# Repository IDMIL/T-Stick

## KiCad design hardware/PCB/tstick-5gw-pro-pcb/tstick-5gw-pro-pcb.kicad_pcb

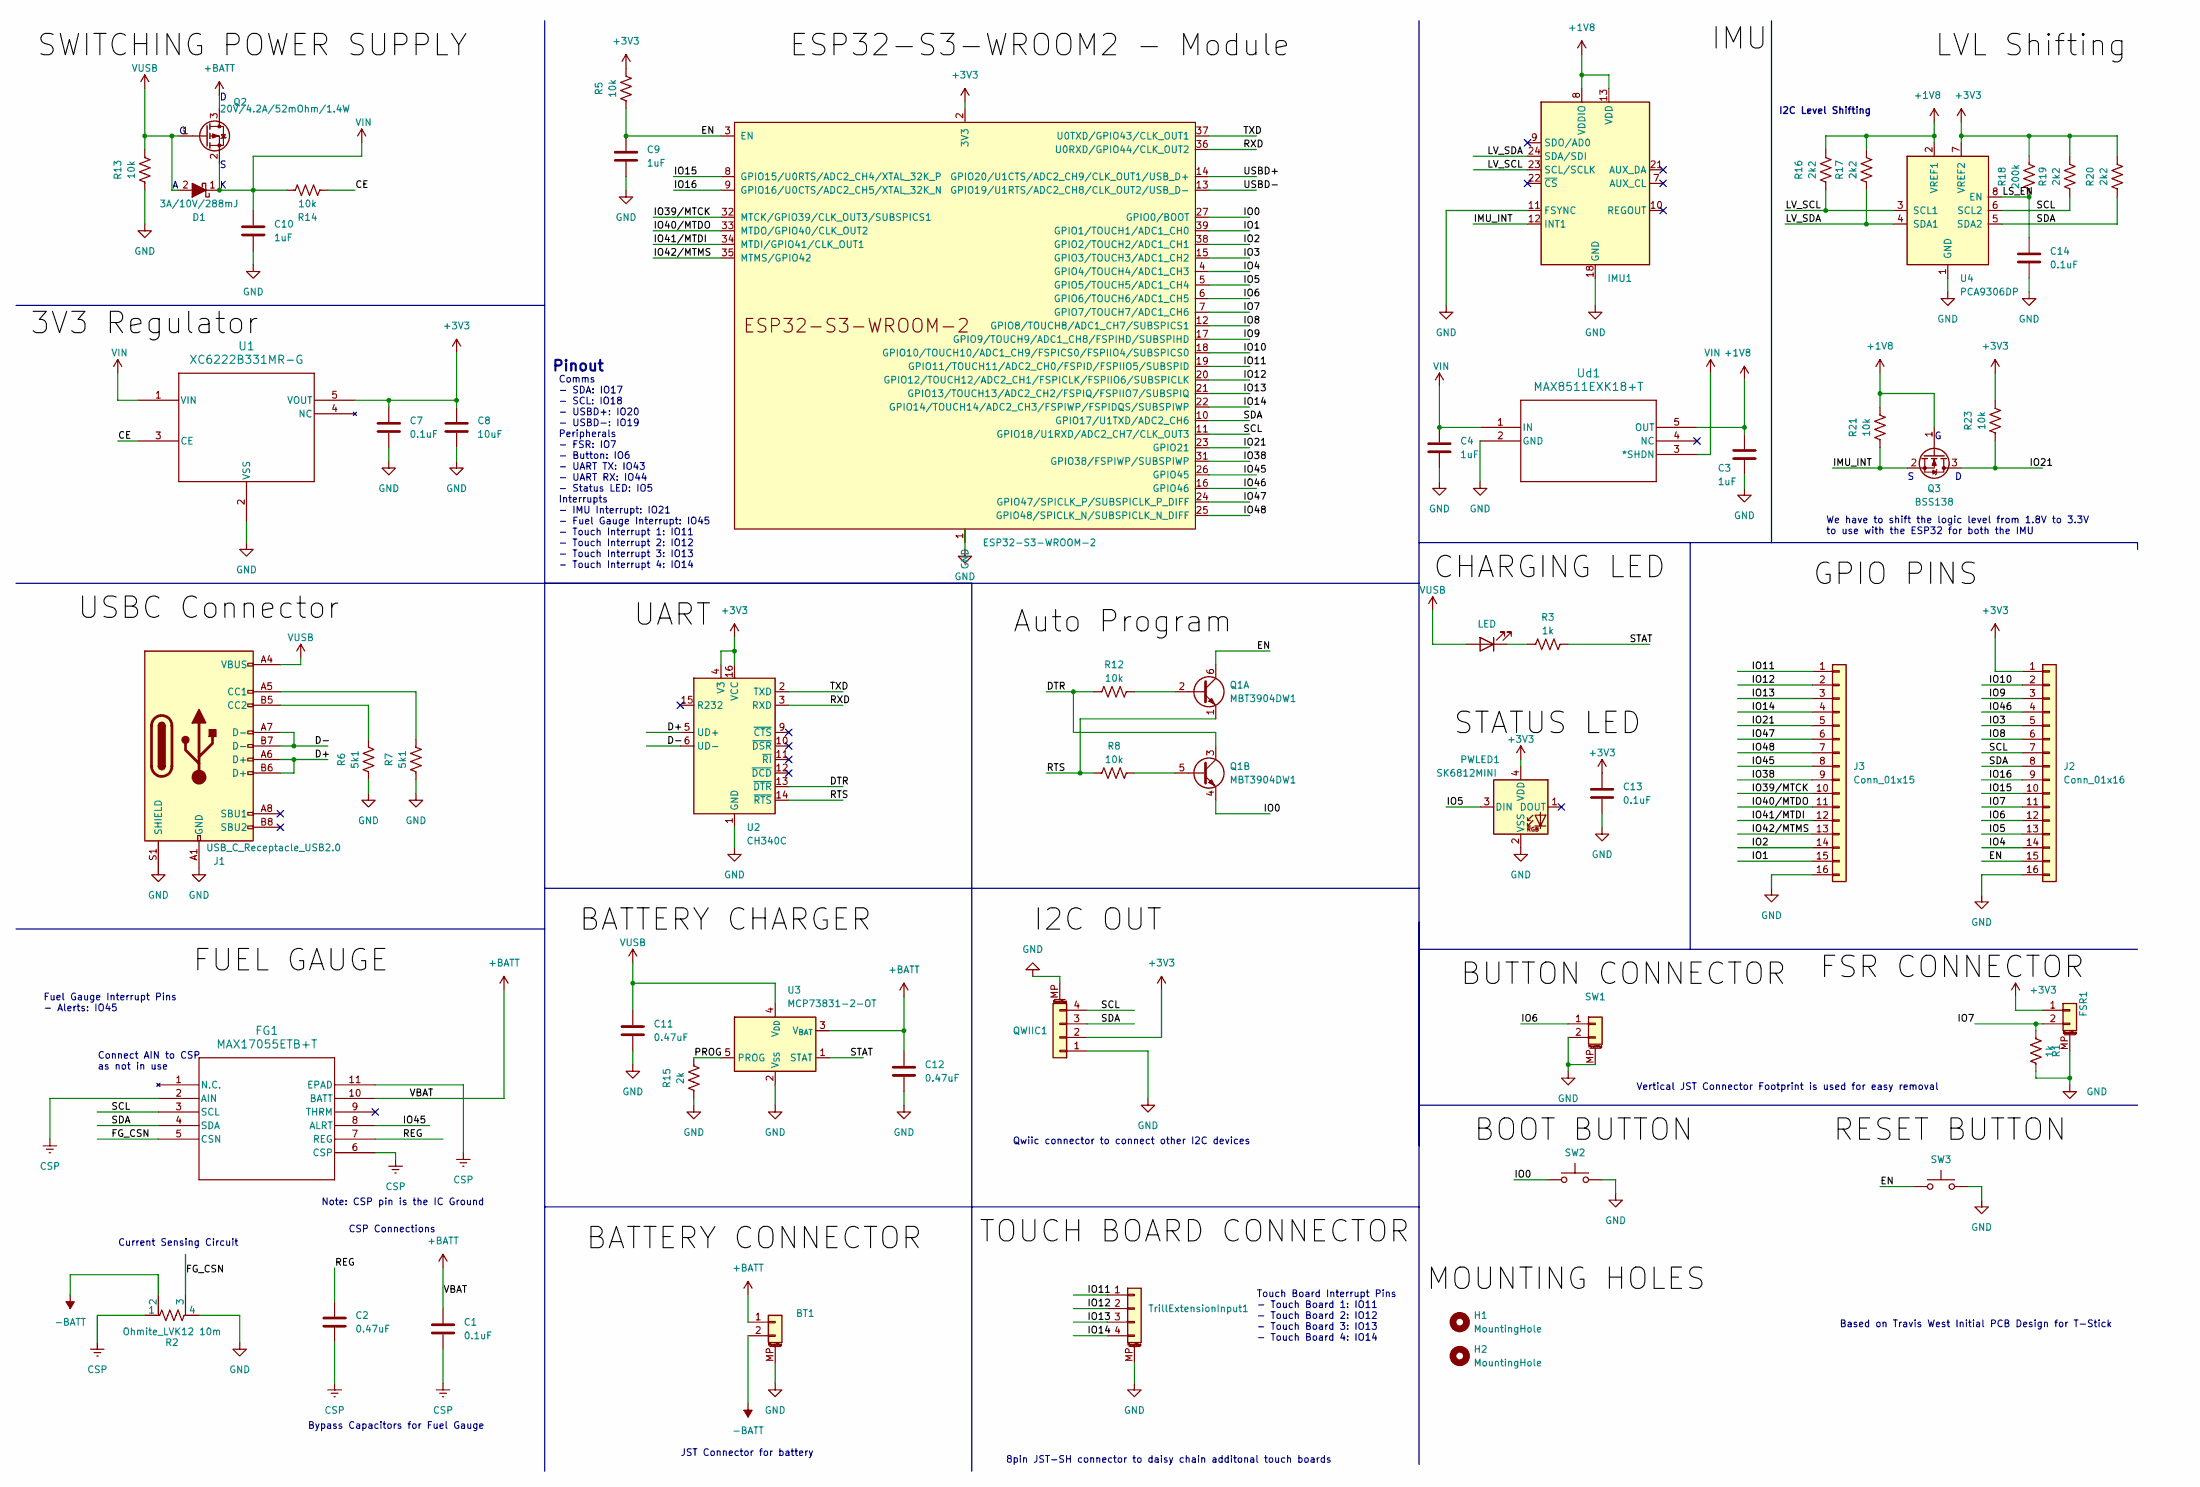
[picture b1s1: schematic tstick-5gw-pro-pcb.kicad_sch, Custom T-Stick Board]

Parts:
BT1: JST-PH-1x02-2.000mm; JST_PH_S2B-PH-SM4-TB_1x02-1MP_P2.00mm_Horizontal; Mfg Part # S2B-PH-SM4-TB; Digikey Part # 455-S2B-PH-SM4-TBTR-ND
C1: 0.1uF; C_0201_0603Metric; Mfg Part # CL03A104KP3NNNC; Digikey Part # 1276-1115-2-ND
C2, C11, C12: 0.47uF; C_0201_0603Metric; Mfg Part # CL03A474KQ3NNNC; Digikey Part # 1276-1337-1-ND
C3, C4: 1uF; C_0201_0603Metric; Mfg Part # CL03A105KQ3CSNC; Digikey Part # 1276-1115-1-ND
C7, C13, C14: 0.1uF; C_0201_0603Metric; Mfg Part # CL03A104KP3NNNC; Digikey Part # 1276-1115-1-ND
C8: 10uF; C_0603_1608Metric; Mfg Part # CL10A106KQ8NNNC; Digikey Part # 1276-1038-1-ND
C9, C10: 1uF; C_0201_0603Metric; Mfg Part # CL03A105KQ3CSNC; Digikey Part # 1276-1323-1-ND
CHARGLED1: LED; LED_0201_0603Metric; Mfg Part # APG0603ZGC-5MAV; Digikey Part # 754-APG0603ZGC-5MAVCT-ND
D1: 3A/10V/288mJ; D_SOD-323; Mfg Part # BAT60BE6327HTSA1; Digikey Part # BAT60BE6327HTSA1CT-ND
FG1: MAX17055ETB+T; 21-100013A_T102A2&plus_1C_MXM; Mfg Part # MAX17055ETB+T; Digikey Part # MAX17055ETB+TCT-ND
FSR1: JST-SH-1.00mm 1x2; JST_SH_BM02B-SRSS-TB_1x02-1MP_P1.00mm_Vertical; Mfg Part # BM02B-SRSS-TB; Digikey Part # 455-1788-1-ND
H1, H2: MountingHole; MountingHole_3.2mm_M3_DIN965
IMU1: ICM-20948; QFN24_3X3X0P9_IVS; Mfg Part # ICM-20948; Digikey Part # 1428-1123-1-ND
J1: USB_C_Receptacle_USB2.0; USB_C_Receptacle_GCT_USB4105-xx-A_16P_TopMnt_Horizontal; Mfg Part # USB4105-GF-A; Digikey Part # 2073-USB4105-GF-ACT-ND
J2: Conn_01x16; PinHeader_1x16_P2.54mm_Vertical
J3: Conn_01x15; PinHeader_1x16_P2.54mm_Vertical
MCU1: ESP32-S3-WROOM-2; Mfg Part # ESP32-S3-WROOM-2-N32R8V; Digikey Part # 1965-ESP32-S3-WROOM-2-N32R8VCT-ND
PWLED1: SK6812MINI; LED_SK6812MINI_PLCC4_3.5x3.5mm_P1.75mm; Mfg Part # Addressable Lighting Neopixel 10 LED Di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; Digikey Part # 1528-1542-ND
Q1: MBT3904DW1; SOT-363_SC-70-6; Mfg Part # MBT3904DW1T1G
Q2: 20V/4.2A/52mOhm/1.4W; SOT-23-3; Mfg Part # SI2305BHE3-TP; Digikey Part # 353-SI2305BHE3-TPCT-ND
Q3: BSS138; SOT-23; Mfg Part # BSS138; Digikey Part # 4530-BSS138CT-ND
QWIIC1: JST-SH-1x04 1.0mm; JST_SH_SM04B-SRSS-TB_1x04-1MP_P1.00mm_Horizontal; Mfg Part # SM04B-SRSS-TB; Digikey Part # 455-1804-1-ND
R1, R3: 1k; R_0201_0603Metric; Mfg Part # ERJ-1GNF1001C; Digikey Part # P122413CT-ND
R2: Ohmite_LVK12 10m; LVK12_OHM-L; Mfg Part # LVK12R010CER; Digikey Part # 273-LVK12R010CERCT-ND
R5, R8, R12, R13, R14, R21, R23: 10k; R_0201_0603Metric; Mfg Part # ERJ-1GNF1002C; Digikey Part # P122414CT-ND
R6, R7: 5k1; R_0201_0603Metric; Mfg Part # ERJ-1GNJ512C; Digikey Part # P123340CT-ND
R15: 2k; R_0201_0603Metric; Mfg Part # ERJ-1GNF2001C; Digikey Part # P122812CT-ND
R16, R17, R19, R20: 2k2; R_0201_0603Metric; Mfg Part # ERJ-1GNF2201C; Digikey Part # P122832CT-ND
R18: 200k; R_0201_0603Metric; Mfg Part # ERJ-1GNF2003C; Digikey Part # P122814CT-ND
SW1: JST-SH-1.00mm 1x2; JST_SH_BM02B-SRSS-TB_1x02-1MP_P1.00mm_Vertical; Mfg Part # BM02B-SRSS-TB; Digikey Part # 455-1788-1-ND
SW2, SW3: PTS810 SJM Switch; SW_SPST_PTS810; Mfg Part # PTS810 SJM 250 SMTR LFS; Digikey Part # CKN10502CT-ND
TrillExtensionInput1: JST-SH 1x08 1.00mm; JST_SH_SM04B-SRSS-TB_1x04-1MP_P1.00mm_Horizontal; Mfg Part # SM04B-SRSS-TB; Digikey Part # 455-3960-1-ND
U1: XC6222B331MR-G; SOT-25_TOR; Mfg Part # XC6222B331MR-G; Digikey Part # 893-1143-1-ND
U2: CH340C; SOIC-16_3.9x9.9mm_P1.27mm; Mfg Part # CH340C
U3: MCP73831-2-OT; SOT-23-5; Mfg Part # MCP73831T-2DCI/OT; Digikey Part # MCP73831T-2DCI/OTDKR-ND
U4: PCA9306DP; TSSOP-8_3x3mm_P0.65mm; Mfg Part # PCA9306DP1,125; Digikey Part # 568-4243-1-ND
Ud1: MAX8511EXK18+T; 21-0076_X5&plus_1_MXM; Mfg Part # MAX8511EXK18+T; Digikey Part # MAX8511EXK18+TTR-ND

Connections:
+1V8: C3.1, IMU1.8 (VDDIO), IMU1.13 (VDD), Q3.1 (G), R16.2, R17.2, R21.2, U4.2 (VREF1), Ud1.5 (OUT)
+3V3: C7.1, C8.1, C13.1, FSR1.1, J2.1, MCU1.2 (3V3), PWLED1.4 (VDD), QWIIC1.2, R5.2, R18.2, R19.2, R20.2, R23.2, U1.5 (VOUT), U2.4 (V3), U2.16 (VCC), U4.7 (VREF2)
+BATT: BT1.1, C1.1, C12.1, FG1.10 (BATT), Q2.3 (D), U3.3 (V_{BAT})
-BATT: BT1.2, R2.2
/CE: R14.1, U1.3 (CE)
/D+: J1.A6 (D+), J1.B6 (D+), U2.5 (UD+)
/D-: J1.A7 (D-), J1.B7 (D-), U2.6 (UD-)
/DTR: Q1.3 (C2), R12.1, U2.13 (~DTR)
/EN: C9.1, J2.15, MCU1.3 (EN), Q1.6 (C1), R5.1, SW3.1
/FG_CSN: FG1.5 (CSN), R2.3
/IMU_INT: IMU1.12 (INT1), Q3.2 (S), R21.1
/IO0: MCU1.27 (GPIO0/BOOT), Q1.4 (E2), SW2.1
/IO1: J3.15, MCU1.39 (GPIO1/TOUCH1/ADC1_CH0)
/IO2: J3.14, MCU1.38 (GPIO2/TOUCH2/ADC1_CH1)
/IO3: J2.5, MCU1.15 (GPIO3/TOUCH3/ADC1_CH2)
/IO4: J2.14, MCU1.4 (GPIO4/TOUCH4/ADC1_CH3)
/IO5: J2.13, MCU1.5 (GPIO5/TOUCH5/ADC1_CH4), PWLED1.3 (DIN)
/IO6: J2.12, MCU1.6 (GPIO6/TOUCH6/ADC1_CH5), SW1.1
/IO7: FSR1.2, J2.11, MCU1.7 (GPIO7/TOUCH7/ADC1_CH6), R1.1
/IO8: J2.6, MCU1.12 (GPIO8/TOUCH8/ADC1_CH7/SUBSPICS1)
/IO9: J2.3, MCU1.17 (GPIO9/TOUCH9/ADC1_CH8/FSPIHD/SUBSPIHD)
/IO10: J2.2, MCU1.18 (GPIO10/TOUCH10/ADC1_CH9/FSPICS0/FSPIIO4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)
/IO11: J3.1, MCU1.19 (GPIO11/TOUCH11/ADC2_CH0/FSPID/FSPIIO5/S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), TrillExtensionInput1.1
/IO12: J3.2, MCU1.20 (GPIO12/TOUCH12/ADC2_CH1/FSPICLK/FSPIIO6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), TrillExtensionInput1.2
/IO13: J3.3, MCU1.21 (GPIO13/TOUCH13/ADC2_CH2/FSPIQ/FSPIIO7/S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), TrillExtensionInput1.3
/IO14: J3.4, MCU1.22 (GPIO14/TOUCH14/ADC2_CH3/FSPIWP/FSPIDQS/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), TrillExtensionInput1.4
/IO15: J2.10, MCU1.8 (GPIO15/U0RTS/ADC2_CH4/XTAL_32K_P)
/IO16: J2.9, MCU1.9 (GPIO16/U0CTS/ADC2_CH5/XTAL_32K_N)
/IO21: J3.5, MCU1.23 (GPIO21), Q3.3 (D), R23.1
/IO38: J3.9, MCU1.31 (GPIO38/FSPIWP/SUBSPIWP)
/IO39/MTCK: J3.10, MCU1.32 (MTCK/GPIO39/CLK_OUT3/SUBSPICS1)
/IO40/MTDO: J3.11, MCU1.33 (MTDO/GPIO40/CLK_OUT2)
/IO41/MTDI: J3.12, MCU1.34 (MTDI/GPIO41/CLK_OUT1)
/IO42/MTMS: J3.13, MCU1.35 (MTMS/GPIO42)
/IO45: FG1.8 (ALRT), J3.8, MCU1.26 (GPIO45)
/IO46: J2.4, MCU1.16 (GPIO46)
/IO47: J3.6, MCU1.24 (GPIO47/SPICLK_P/SUBSPICLK_P_DIFF)
/IO48: J3.7, MCU1.25 (GPIO48/SPICLK_N/SUBSPICLK_N_DIFF)
/LS_EN: C14.1, R18.1, U4.8 (EN)
/LV_SCL: IMU1.23 (SCL/SCLK), R16.1, U4.3 (SCL1)
/LV_SDA: IMU1.24 (SDA/SDI), R17.1, U4.4 (SDA1)
/PROG: R15.2, U3.5 (PROG)
/REG: C2.1, FG1.7 (REG)
/RTS: Q1.1 (E1), R8.1, U2.14 (~RTS)
/RXD: MCU1.36 (U0RXD/GPIO44/CLK_OUT2), U2.3 (RXD)
/SCL: FG1.3 (SCL), J2.7, MCU1.11 (GPIO18/U1RXD/ADC2_CH7/CLK_OUT3), QWIIC1.4, R19.1, U4.6 (SCL2)
/SDA: FG1.4 (SDA), J2.8, MCU1.10 (GPIO17/U1TXD/ADC2_CH6), QWIIC1.3, R20.1, U4.5 (SDA2)
/STAT: R3.2, U3.1 (STAT)
/TXD: MCU1.37 (U0TXD/GPIO43/CLK_OUT1), U2.2 (TXD)
/USBD+: MCU1.14 (GPIO20/U1CTS/ADC2_CH9/CLK_OUT1/USB_D+)
/USBD-: MCU1.13 (GPIO19/U1RTS/ADC2_CH8/CLK_OUT2/USB_D-)
CSP: C1.2, C2.2, FG1.2 (AIN), FG1.6 (CSP), FG1.11 (EPAD), R2.1
GND: BT1.MP (MountPin), C3.2, C4.2, C7.2, C8.2, C9.2, C10.2, C11.2, C12.2, C13.2, C14.2, FSR1.MP (MountPin), IMU1.11 (FSYNC), IMU1.18 (GND), IMU1.20 (GND), J1.A1 (GND), J1.A12 (GND), J1.B1 (GND), J1.B12 (GND), J1.S1 (SHIELD), J2.16, J3.16, MCU1.1 (GND), MCU1.40 (GND), MCU1.41 (GND), PWLED1.2 (VSS), QWIIC1.1, QWIIC1.MP (MountPin), R1.2, R2.4, R6.1, R7.1, R13.1, R15.1, SW1.2, SW1.MP (MountPin), SW2.2, SW3.2, TrillExtensionInput1.MP (MountPin), U1.2 (VSS), U2.1 (GND), U3.2 (V_{SS}), U4.1 (GND), Ud1.2 (GND)
unnamed: CHARGLED1.1 (K), R3.1
unnamed: J1.A5 (CC1), R7.2
unnamed: J1.B5 (CC2), R6.2
unnamed: Q1.2 (B1), R12.2
unnamed: Q1.5 (B2), R8.2
VIN: C4.1, C10.1, D1.1 (K), Q2.2 (S), R14.2, U1.1 (VIN), Ud1.1 (IN), Ud1.3 (*SHDN)
VUSB: C11.1, CHARGLED1.2 (A), D1.2 (A), J1.A4 (VBUS), J1.A9 (VBUS), J1.B4 (VBUS), J1.B9 (VBUS), Q2.1 (G), R13.2, U3.4 (V_{DD})

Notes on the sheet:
Comms - SDA: IO17 - SCL: IO18 - USBD+: IO20 - USBD-: IO19 Peripherals - FSR: IO7 - Button: IO6 - UART TX: IO43 - UART RX: IO44 - Status LED: IO5 Interrupts - IMU Interrupt: IO21 - Fuel Gauge Interrupt: IO45 - Touch Interrupt 1: IO11 - Touch Interrupt 2: IO12 - Touch Interrupt 3: IO13 - Touch Interr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
Connect AIN to CSP as not in use
Qwiic connector to connect other I2C devices
Fuel Gauge Interrupt Pins - Alerts: IO45
JST Connector for battery
Current Sensing Circuit
I2C Level Shifting
Bypass Capacitors for Fuel Gauge
Vertical JST Connector Footprint is used for easy removal
Touch Board Interrupt Pins - Touch Board 1: IO11 - Touch Board 2: IO12 - Touch Board 3: IO13 - Touch Board 4: IO14
Based on Travis West Initial PCB Design for T-Stick
8pin JST-SH connector to daisy chain additonal touch boards
CSP Connections
Note: CSP pin is the IC Ground
Pinout
We have to shift the logic level from 1.8V to 3.3V to use with the ESP32 for both the IMU

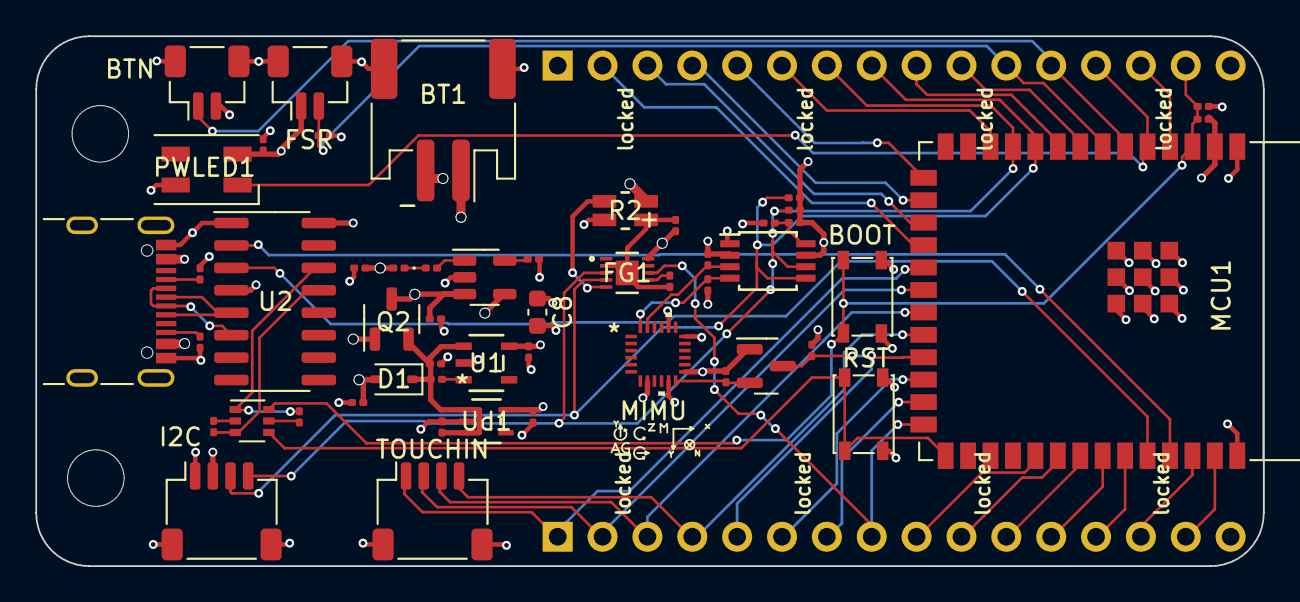
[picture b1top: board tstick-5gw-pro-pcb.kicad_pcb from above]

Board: 4 copper layers, 69.5 x 30.0 mm, 56 parts (0 on the bottom side), 58 nets.

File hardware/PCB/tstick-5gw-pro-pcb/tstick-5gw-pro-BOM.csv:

Manufacturer,Mfg Part #,Description Value Pkg,Reference(s),Qty
JST Sales America Inc.,S2B-PH-SM4-TB,"Connector Header Surface Mount, Right Angle 2 position 0.079"" (2.00mm)",BT1,1
Samsung Electro-Mechanics,CL03A104KP3NNNC,0.1 µF ±10% 10V Ceramic Capacitor X5R 0201 (0603 Metric),"C1, C7, C13, C14",4
Samsung Electro-Mechanics,CL03A474KQ3NNNC,0.47 µF ±10% 6.3V Ceramic Capacitor X5R 0201 (0603 Metric),"C2, C11, C12",3
Samsung Electro-Mechanics,CL03A105KQ3CSNC,1 µF ±10% 6.3V Ceramic Capacitor X5R 0201 (0603 Metric),"C3, C4, C9, C10",4
Samsung Electro-Mechanics,CL10A106KQ8NNNC,10 µF ±10% 6.3V Ceramic Capacitor X5R 0603 (1608 Metric),C8,1
Kingbright,APG0603ZGC-5MAV,Green 525nm LED Indication - Discrete 2.85V 0201 (0603 Metric),CHARGLED1,1
Infineon Technologies,BAT60BE6327HTSA1,Diode 10 V 3A Surface Mount PG-SOD323-3D,D1,1
Analog Devices Inc./Maxim Integrated,MAX17055ETB+T,Battery Battery Monitor IC Multi-Chemistry 10-TDFN (2.5x2),FG1,1
JST Sales America Inc.,BM02B-SRSS-TB,"Connector Header Surface Mount 2 position 0.039"" (1.00mm)","FSR1, SW1",2
TDK InvenSense,ICM-20948,"Accelerometer, Gyroscope, Magnetometer, 9 Axis Sensor IÂ²C, SPI Output",IMU1,1
GCT,USB4105-GF-A,"USB-C (USB TYPE-C) USB 2.0 Receptacle Connector 24 (16+8 Dummy) Position Surface Mount, Right Angle; Through Hole",J1,1
Espressif Systems,ESP32-S3-WROOM-2-N32R8V,"Bluetooth, WiFi 802.11b/g/n, Bluetooth v5.0 Transceiver Module 2.4GHz PCB Trace Surface Mount",MCU1,1
Adafruit Industries LLC,2659,"Addressable Lighting Neopixel 10 LED Discrete Serial (Shift Register) Red, Green, Blue (RGB) 3.50mm L x 3.50mm W ",PWLED1,1
onsemi,MBT3904DW1T1G,Bipolar (BJT) Transistor Array 2 NPN (Dual) 40V 200mA 300MHz 150mW Surface Mount SC-88/SC70-6/SOT-363,Q1,1
Micro Commercial Co,SI2305BHE3-TP,P-Channel 20 V 4.2A 1.4W Surface Mount SOT-23,Q2,1
ANBON SEMICONDUCTOR (INT'L) LIMITED,BSS138,N-Channel 50 V 220mA (Ta) 350mW (Ta) Surface Mount SOT-23,Q3,1
JST Sales America Inc.,SM04B-SRSS-TB,"Connector Header Surface Mount, Right Angle 4 position 0.039"" (1.00mm)",QWIIC1,1
Panasonic Electronic Components,ERJ-1GNF1001C,"1 kOhms Â±1% 0.05W, 1/20W Chip Resistor 0201 (0603 Metric) Thick Film","R1, R3",2
Ohmite,LVK12R010CER,"10 mOhms Â±0.25% 0.5W, 1/2W Chip Resistor 1206 (3216 Metric) Anti-Corrosive, Current Sense, Moisture Resistant Thick Film",R2,1
Panasonic Electronic Components,ERJ-1GNF1002C,"10 kOhms Â±1% 0.05W, 1/20W Chip Resistor 0201 (0603 Metric) Thick Film","R5, R8, R12, R13, R14, R21, R23",7
Panasonic Electronic Components,ERJ-1GNJ512C,"5.1 kOhms Â±5% 0.05W, 1/20W Chip Resistor 0201 (0603 Metric) Thick Film","R6, R7",2
Panasonic Electronic Components,ERJ-1GNF2001C,"2 kOhms Â±1% 0.05W, 1/20W Chip Resistor 0201 (0603 Metric) Thick Film",R15,1
Panasonic Electronic Components,ERJ-1GNF2201C,"2.2 kOhms Â±1% 0.05W, 1/20W Chip Resistor 0201 (0603 Metric) Thick Film","R16, R17, R19, R20",4
Panasonic Electronic Components,ERJ-1GNF2003C,"200 kOhms Â±1% 0.05W, 1/20W Chip Resistor 0201 (0603 Metric) Thick Film",R18,1
C&K,PTS810 SJM 250 SMTR LFS,Tactile Switch SPST-NO Top Actuated Surface Mount,"SW2, SW3",2
JST Sales America Inc.,SM04B-SRSS-TB,"Connector Header Surface Mount, Right Angle 4 position 0.039"" (1.00mm)",TrillExtensionInput1,1
Torex Semiconductor Ltd,XC6222B331MR-G,Linear Voltage Regulator IC Positive Fixed 1 Output 700mA SOT-25-5,U1,1
WCH,CH340C,USB to serial chip CH340C,U2,1
Microchip Technology,MCP73831T-2DCI/OT,Charger IC Lithium Ion/Polymer SOT-23-5,U3,1
NXP USA Inc.,"PCA9306DP1,125",Voltage Level Translator Bidirectional 1 Circuit 2 Channel 8-TSSOP,U4,1
Analog Devices Inc./Maxim Integrated,MAX8511EXK18+T,Linear Voltage Regulator IC Positive Fixed 1 Output 120mA SC-70-5,Ud1,1

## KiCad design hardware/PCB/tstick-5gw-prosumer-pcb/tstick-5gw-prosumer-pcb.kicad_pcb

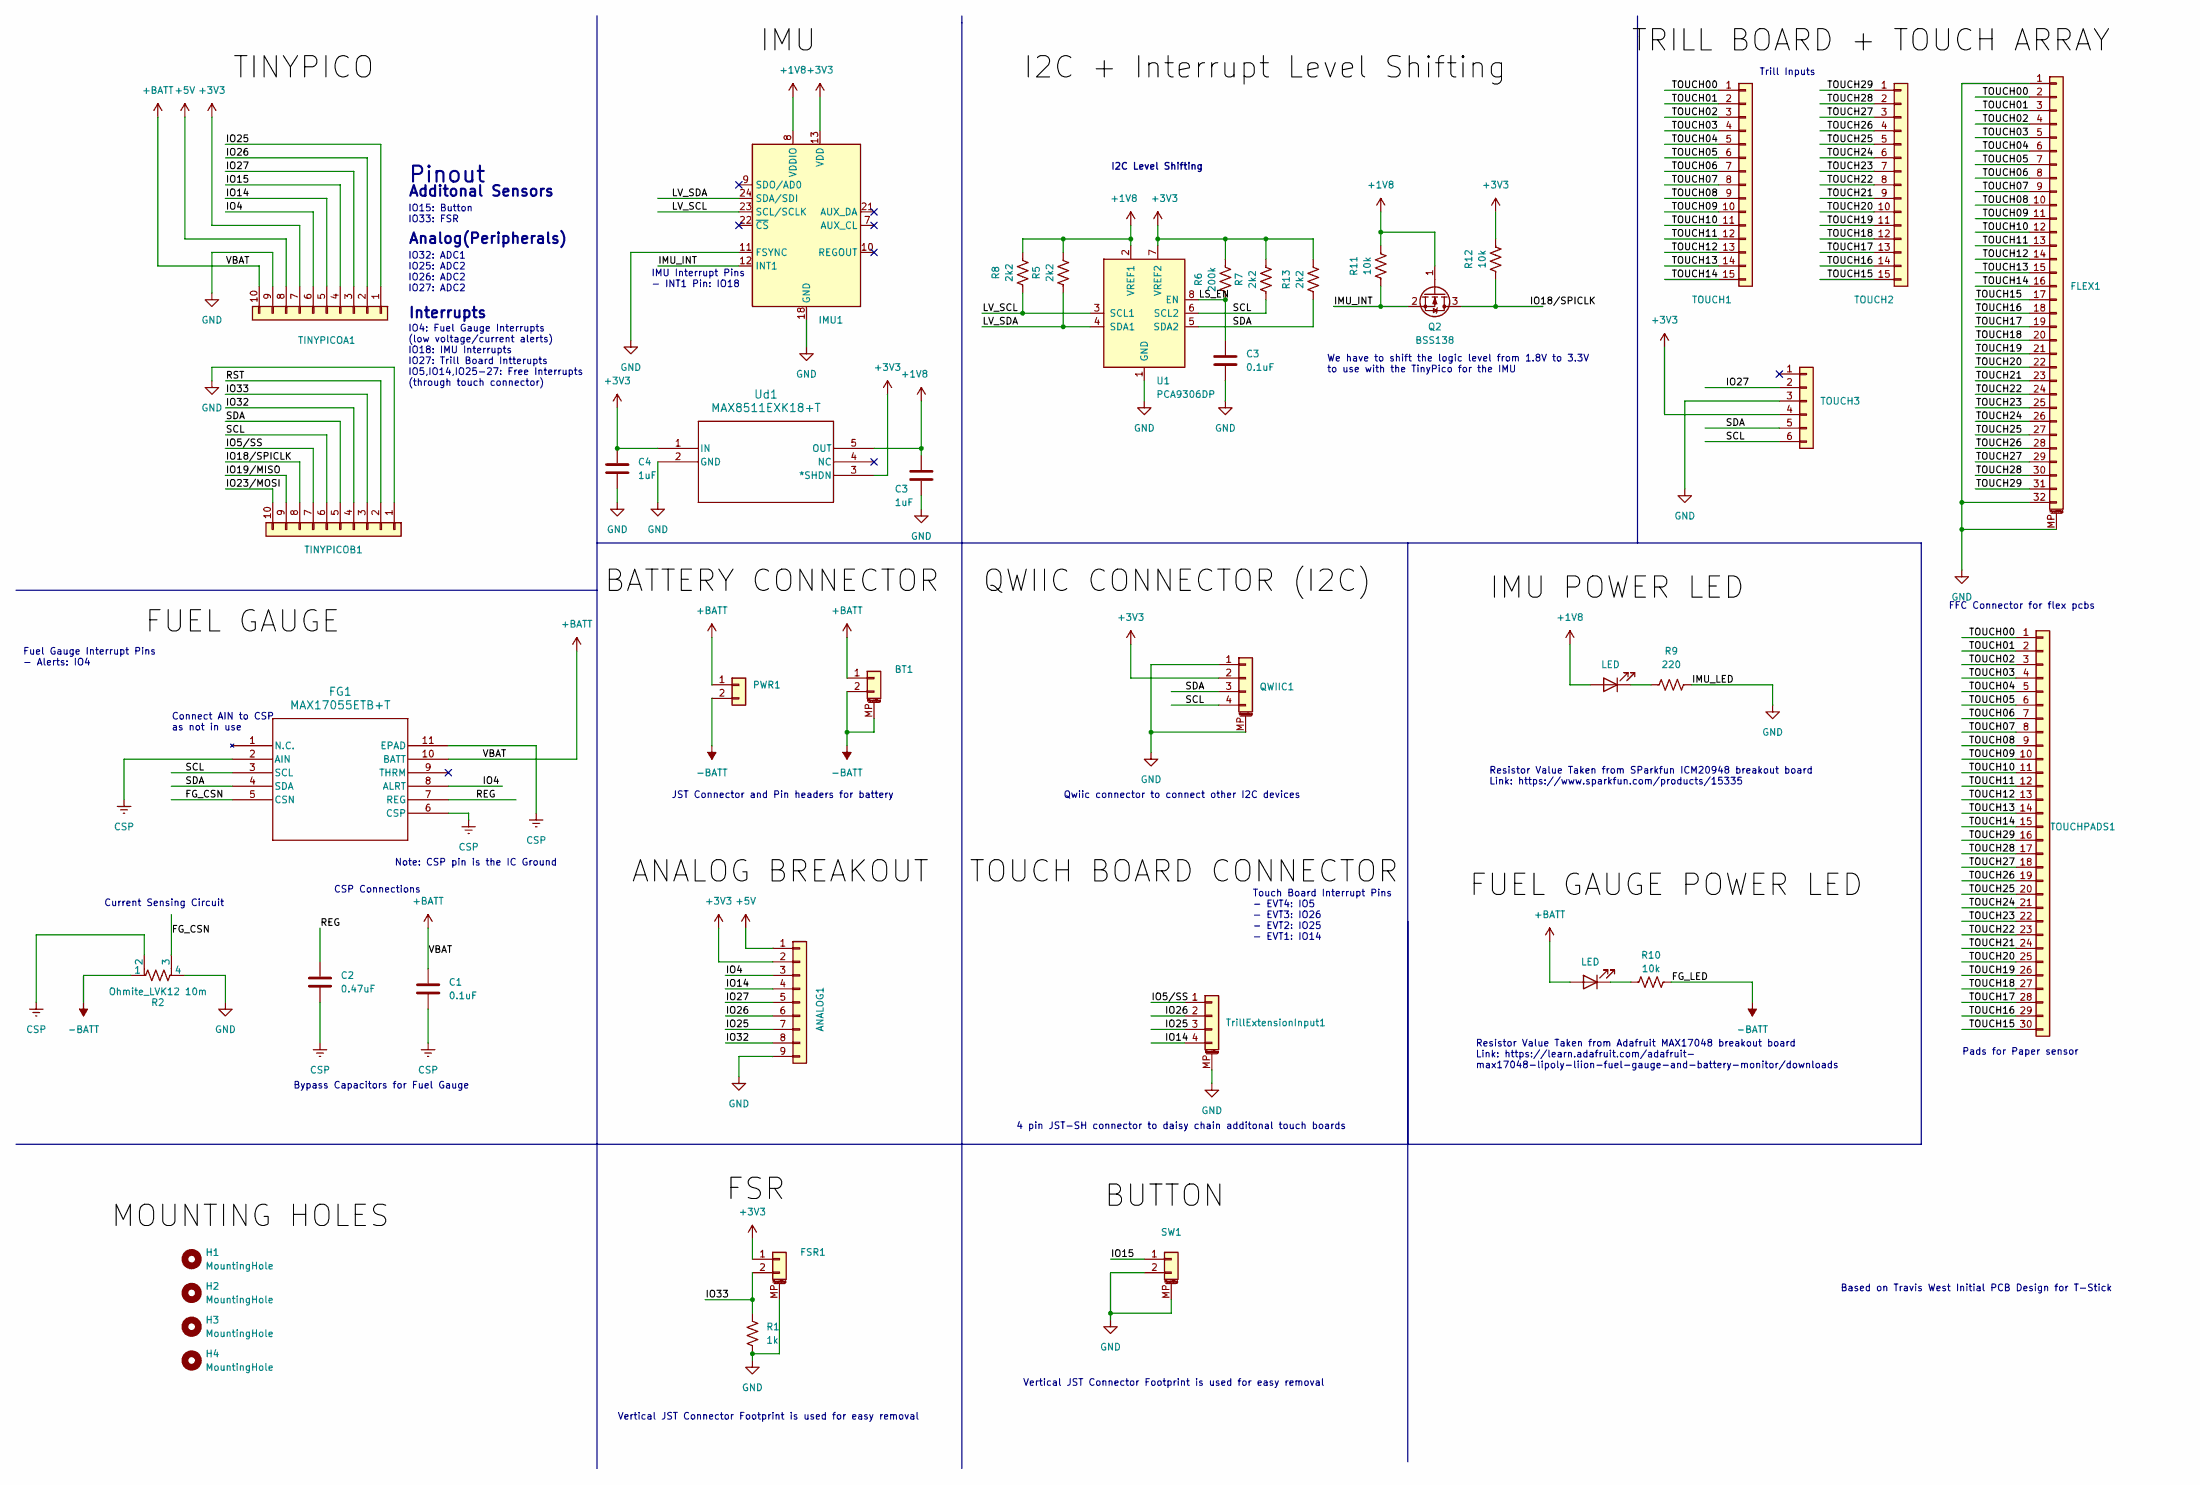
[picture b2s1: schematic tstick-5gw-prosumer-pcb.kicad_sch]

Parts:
ANALOG1: Conn_01x09; PinHeader_1x09_P2.54mm_Vertical_SMD_Pin1Left; Mfg Part # SSM-109-L-SV; Digikey Part # SAM1148-09-ND
BT1: JST-PH-1x02-2.000mm; JST_PH_S2B-PH-SM4-TB_1x02-1MP_P2.00mm_Horizontal; Mfg Part # S2B-PH-SM4-TB; Digikey Part # 455-S2B-PH-SM4-TBCT-ND
C1, C3: 0.1uF; C_0201_0603Metric; Mfg Part # CL03A104KP3NNNC; Digikey Part # 1276-1115-1-ND
C2: 0.47uF; C_0201_0603Metric; Mfg Part # CL03A474KQ3NNNC; Digikey Part # 1276-1337-1-ND
C4: 1uF; C_0201_0603Metric; Mfg Part # CL03A105KQ3CSNC; Digikey Part # 1276-1115-1-ND
FG1: MAX17055ETB+T; 21-100013A_T102A2&plus_1C_MXM; Mfg Part # MAX17055ETB+T; Digikey Part # MAX17055ETB+TCT-ND
FLEX1: Conn_01x32; CON_541323262_MOL; Mfg Part # 0541323262; Digikey Part # 900-0541323262CT-ND
FSR1: JSTCONNECTOR; JST_SH_BM02B-SRSS-TB_1x02-1MP_P1.00mm_Vertical; Mfg Part # BM02B-SRSS-TB; Digikey Part # 455-1788-1-ND
H1, H2, H3, H4: MountingHole; MountingHole_3.2mm_M3_DIN965
IMU1: ICM-20948; QFN24_3X3X0P9_IVS; Mfg Part # ICM-20948; Digikey Part # 1428-1123-1-ND
LED1: LED; LED_0402_1005Metric; Mfg Part # APHHS1005LSECK/J3-PF; Digikey Part # 754-2123-1-ND
LED2: LED; LED_0402_1005Metric; Mfg Part # APHHS1005CGCK; Digikey Part # APHHS1005CGCK
PWR1: Conn_01x02; SolderPad
Q2: BSS138; SOT-23; Mfg Part # BSS138; Digikey Part # 4530-BSS138CT-ND
QWIIC1: JST-SH-1x04 1.0mm; JST_SH_SM04B-SRSS-TB_1x04-1MP_P1.00mm_Horizontal; Mfg Part # SM04B-SRSS-TB(LF)(SN); Digikey Part # 455-1804-1-ND
R1: 1k; R_0201_0603Metric; Mfg Part # ERJ-1GNF1001C; Digikey Part # P122413CT-ND
R2: Ohmite_LVK12 10m; R_Shunt_Ohmite_LVK12; Mfg Part # LVK12R010CER; Digikey Part # 273-LVK12R010CERCT-ND
R5, R7, R8, R13: 2k2; R_0201_0603Metric; Mfg Part # ERJ-1GNF2201C; Digikey Part # P122832CT-ND
R6: 200k; R_0201_0603Metric; Mfg Part # ERJ-1GNF2003C; Digikey Part # P122814CT-ND
R9: 220; R_0201_0603Metric; Mfg Part # ERJ-1GNJ221C; Digikey Part # P123276CT-ND
R10, R11, R12: 10k; R_0201_0603Metric; Mfg Part # ERJ-1GNF1002C; Digikey Part # P122414CT-ND
SW1: JSTCONNECTOR; JST_SH_BM02B-SRSS-TB_1x02-1MP_P1.00mm_Vertical; Mfg Part # BM02B-SRSS-TB; Digikey Part # 455-1788-1-ND
TINYPICOA1: Conn_01x10; PinHeader_1x10_P2.54mm_Vertical_SMD_Pin1Left; Mfg Part # SSM-110-L-SV-P-TR; Digikey Part # SAM14613CT-ND
TINYPICOB1: Conn_01x10; PinHeader_1x10_P2.54mm_Vertical_SMD_Pin1Left; Mfg Part # SSM-110-L-SV-P-TR; Digikey Part # SAM14613CT-ND
TOUCH1, TOUCH2: Conn_01x15; PinHeader_1x15_P2.54mm_Vertical_SMD_Pin1Left; Mfg Part # SSM-115-L-SV; Digikey Part # SAM1148-15-ND
TOUCH3: Conn_01x06; PinHeader_1x06_P2.54mm_Vertical_SMD_Pin1Left; Mfg Part # SSM-106-F-SV; Digikey Part # SSM-106-F-SV
TOUCHPADS1: Conn_01x30; TOUCHSENSORPAD
TrillExtensionInput1: JST-SH 1x08 1.00mm; JST_SH_SM04B-SRSS-TB_1x04-1MP_P1.00mm_Horizontal; Mfg Part # SM04B-SRSS-TB(LF)(SN); Digikey Part # 455-1804-1-ND
U1: PCA9306DP; TSSOP-8_3x3mm_P0.65mm; Mfg Part # PCA9306DP1,125; Digikey Part # 568-4243-1-ND
Ud1: MAX8511EXK18+T; 21-0076_X5&plus_1_MXM; Mfg Part # MAX8511EXK18+T; Digikey Part # MAX8511EXK18+TTR-ND

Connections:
+3V3: ANALOG1.2, C4.1, FSR1.1, IMU1.13 (VDD), QWIIC1.2, R6.2, R7.2, R12.2, R13.2, TINYPICOA1.7, TOUCH3.4, U1.7 (VREF2), Ud1.1 (IN), Ud1.3 (*SHDN)
+5V: ANALOG1.1, TINYPICOA1.8
+BATT: BT1.1, C1.1, FG1.10 (BATT), LED2.2 (A), PWR1.1, TINYPICOA1.10
-BATT: BT1.2, BT1.MP (MountPin), PWR1.2, R2.1, R10.2
/FG_CSN: FG1.5 (CSN), R2.3
/IMU_INT: IMU1.12 (INT1), Q2.2 (S), R11.1
/IO4: ANALOG1.3, FG1.8 (ALRT), TINYPICOA1.6
/IO5/SS: TINYPICOB1.7; also elsewhere on the board
/IO14: ANALOG1.4, TINYPICOA1.5; also elsewhere on the board
/IO15: SW1.1, TINYPICOA1.4
/IO18/SPICLK: Q2.3 (D), R12.1, TINYPICOB1.8
/IO19/MISO: TINYPICOB1.9
/IO23/MOSI: TINYPICOB1.10
/IO25: ANALOG1.7, TINYPICOA1.1; also elsewhere on the board
/IO26: ANALOG1.6, TINYPICOA1.2; also elsewhere on the board
/IO27: ANALOG1.5, TINYPICOA1.3, TOUCH3.2
/IO32: ANALOG1.8, TINYPICOB1.4
/IO33: FSR1.2, R1.1, TINYPICOB1.3
/LV_SCL: IMU1.23 (SCL/SCLK), R8.1, U1.3 (SCL1)
/LV_SDA: IMU1.24 (SDA/SDI), R5.1, U1.4 (SDA1)
/REG: C2.1, FG1.7 (REG)
/RST: TINYPICOB1.2
/SCL: FG1.3 (SCL), QWIIC1.4, R7.1, TINYPICOB1.6, TOUCH3.6, U1.6 (SCL2)
/SDA: FG1.4 (SDA), QWIIC1.3, R13.1, TINYPICOB1.5, TOUCH3.5, U1.5 (SDA2)
/TOUCH00: FLEX1.2, TOUCH1.1, TOUCHPADS1.1
/TOUCH01: FLEX1.3, TOUCH1.2, TOUCHPADS1.2
/TOUCH02: FLEX1.4, TOUCH1.3, TOUCHPADS1.3
/TOUCH03: FLEX1.5, TOUCH1.4, TOUCHPADS1.4
/TOUCH04: FLEX1.6, TOUCH1.5, TOUCHPADS1.5
/TOUCH05: FLEX1.7, TOUCH1.6, TOUCHPADS1.6
/TOUCH06: FLEX1.8, TOUCH1.7, TOUCHPADS1.7
/TOUCH07: FLEX1.9, TOUCH1.8, TOUCHPADS1.8
/TOUCH08: FLEX1.10, TOUCH1.9, TOUCHPADS1.9
/TOUCH09: FLEX1.11, TOUCH1.10, TOUCHPADS1.10
/TOUCH10: FLEX1.12, TOUCH1.11, TOUCHPADS1.11
/TOUCH11: FLEX1.13, TOUCH1.12, TOUCHPADS1.12
/TOUCH12: FLEX1.14, TOUCH1.13, TOUCHPADS1.13
/TOUCH13: FLEX1.15, TOUCH1.14, TOUCHPADS1.14
/TOUCH14: FLEX1.16, TOUCH1.15, TOUCHPADS1.15
/TOUCH15: FLEX1.17, TOUCH2.15, TOUCHPADS1.30
/TOUCH16: FLEX1.18, TOUCH2.14, TOUCHPADS1.29
/TOUCH17: FLEX1.19, TOUCH2.13, TOUCHPADS1.28
/TOUCH18: FLEX1.20, TOUCH2.12, TOUCHPADS1.27
/TOUCH19: FLEX1.21, TOUCH2.11, TOUCHPADS1.26
/TOUCH20: FLEX1.22, TOUCH2.10, TOUCHPADS1.25
/TOUCH21: FLEX1.23, TOUCH2.9, TOUCHPADS1.24
/TOUCH22: FLEX1.24, TOUCH2.8, TOUCHPADS1.23
/TOUCH23: FLEX1.25, TOUCH2.7, TOUCHPADS1.22
/TOUCH24: FLEX1.26, TOUCH2.6, TOUCHPADS1.21
/TOUCH25: FLEX1.27, TOUCH2.5, TOUCHPADS1.20
/TOUCH26: FLEX1.28, TOUCH2.4, TOUCHPADS1.19
/TOUCH27: FLEX1.29, TOUCH2.3, TOUCHPADS1.18
/TOUCH28: FLEX1.30, TOUCH2.2, TOUCHPADS1.17
/TOUCH29: FLEX1.31, TOUCH2.1, TOUCHPADS1.16
CSP: C1.2, C2.2, FG1.2 (AIN), FG1.6 (CSP), FG1.11 (EPAD), R2.2
GND: ANALOG1.9, C3.2, C4.2, FLEX1.1, FLEX1.32, FLEX1.MP (MountPin), FSR1.MP (MountPin), IMU1.11 (FSYNC), IMU1.18 (GND), IMU1.20 (GND), QWIIC1.1, QWIIC1.MP (MountPin), R1.2, R2.4, R9.2, SW1.2, SW1.MP (MountPin), TINYPICOA1.9, TINYPICOB1.1, TOUCH3.3, U1.1 (GND), Ud1.2 (GND); also elsewhere on the board
unnamed: LED1.1 (K), R9.1
unnamed: LED2.1 (K), R10.1

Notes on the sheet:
Trill Inputs
Connect AIN to CSP as not in use
Qwiic connector to connect other I2C devices
Pinout
Fuel Gauge Interrupt Pins - Alerts: IO4
IO15: Button IO33: FSR
Additonal Sensors
Analog(Peripherals)
JST Connector and Pin headers for battery
Current Sensing Circuit
Resistor Value Taken from Adafruit MAX17048 breakout board Link: https://learn.adafruit.com/adafruit- max17048-lipoly-liion-fuel-gauge-and-battery-monitor/downloads
IO32: ADC1 IO25: ADC2 IO26: ADC2 IO27: ADC2
IMU Interrupt Pins - INT1 Pin: IO18
FFC Connector for flex pcbs
IO4: Fuel Gauge Interrupts (low voltage/current alerts) IO18: IMU Interrupts IO27: Trill Board Intterupts IO5,IO14,IO25-27: Free Interrupts (through touch connector)
Vertical JST Connector Footprint is used for easy removal
We have to shift the logic level from 1.8V to 3.3V to use with the TinyPico for the IMU
Bypass Capacitors for Fuel Gauge
Interrupts
Touch Board Interrupt Pins - EVT4: IO5 - EVT3: IO26 - EVT2: IO25 - EVT1: IO14
Based on Travis West Initial PCB Design for T-Stick
Resistor Value Taken from SParkfun ICM20948 breakout board Link: https://www.sparkfun.com/products/15335
4 pin JST-SH connector to daisy chain additonal touch boards
CSP Connections
Note: CSP pin is the IC Ground
I2C Level Shifting
Pads for Paper sensor

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
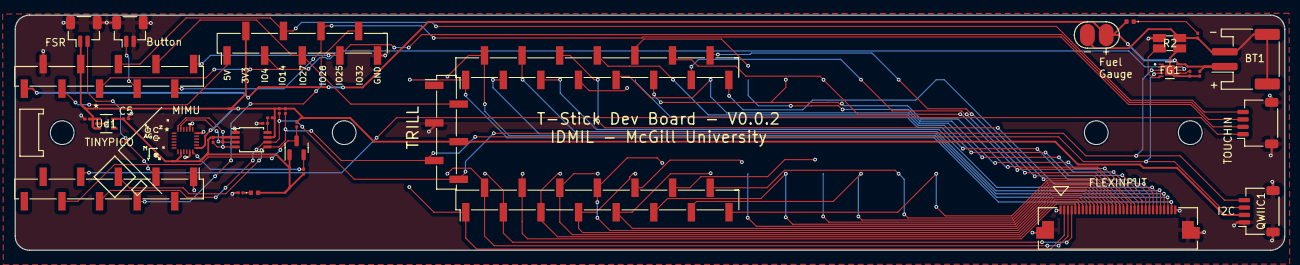
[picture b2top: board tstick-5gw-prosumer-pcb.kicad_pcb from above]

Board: 2 copper layers, 171.5 x 31.8 mm, 41 parts (1 on the bottom side), 57 nets.

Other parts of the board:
C5: 1uF; C_0201_0603Metric
TrillInput1: JST-SH 1x08 1.00mm; JST_SH_SM04B-SRSS-TB_1x04-1MP_P1.00mm_Horizontal

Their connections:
/IO5/SS: TrillInput1.1; also elsewhere on the board
/IO14: TrillInput1.4; also elsewhere on the board
/IO25: TrillInput1.3; also elsewhere on the board
/IO26: TrillInput1.2; also elsewhere on the board
GND: C5.2, TrillInput1.MP (MountPin); also elsewhere on the board
